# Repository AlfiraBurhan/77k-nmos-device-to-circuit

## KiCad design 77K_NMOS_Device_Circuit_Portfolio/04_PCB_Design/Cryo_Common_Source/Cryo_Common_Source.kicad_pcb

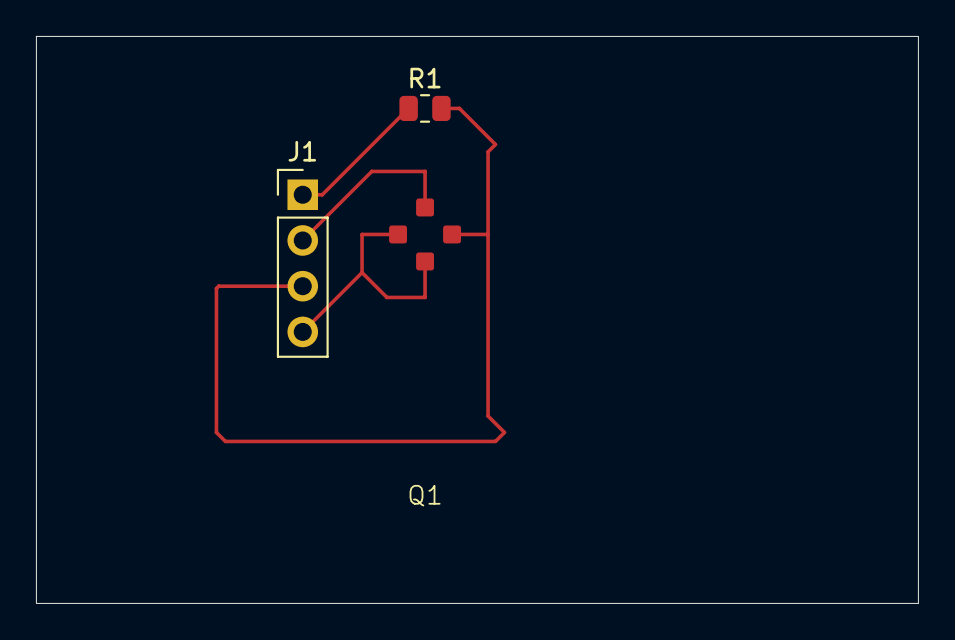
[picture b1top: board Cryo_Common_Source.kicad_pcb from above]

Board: 2 copper layers, 49.0 x 31.5 mm, 3 parts (0 on the bottom side), 4 nets.

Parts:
J1: Conn_01x04_Pin; PinHeader_1x04_P2.54mm_Vertical
Q1: NMOS_Substrate; SKY130_NMOS_DIE_BOND_V2
R1: 9k; R_0805_2012Metric

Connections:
/VIN: J1.2, Q1.2 (G)
/Vout: J1.3, Q1.1 (D), R1.2
GND: J1.4, Q1.3 (S), Q1.4 (Bulk)
VDD: J1.1, R1.1
